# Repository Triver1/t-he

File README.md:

# Tot-HE-m

Tot-HE-m is a hall-effect version of [GEIGEIGEIST's TOTEM](https://github.com/GEIGEIGEIST/TOTEM): the same
38-key split layout, scaled to MX spacing, with a linear hall sensor under every switch instead of a mechanical
contact. The goal is an analog keyboard that is cheap and easy to build at home. Each half is one two-layer PCB
with a handful of SMD parts, a Seeed XIAO RP2040 and a 3D printed case, so everything can be ordered from LCSC,
JLCPCB and the usual keyboard shops, and soldered with an ordinary iron.

## Features

- **Hall-effect sensing on every key**, read through three 74HC4051 multiplexers per half. Tested with MMD C1
  switches; other MX-style magnetic switches (Gateron KS-20, Wooting Lekker and similar) should work as well.
- **Auto calibration.** Each key measures its rest position at power-up and learns where it bottoms out while you
  type; the learnt travel is kept across reboots.
- **Adjustable actuation and release points**, set as key depth in tenths of a millimetre.
- **Rapid trigger**, with separate press and release sensitivity.
- **VIA support**: remap keys and change all of the above live from the browser.
- **Controller layer**: turns W A S D into an analog gamepad stick, so a light press walks and a full press runs.

## Cost

Rough prices for one keyboard, checked October 2026, in euros, before shipping and taxes. Several parts only come
in larger quantities, so ordering for two or more keyboards brings the price per board down a lot.

| Part | Where | Approx. |
| --- | --- | ---: |
| PCBs (5 sets) | JLCPCB | 30 |
| Sensors, muxes, capacitors, TRRS jacks | LCSC | 15 |
| 2x Seeed XIAO RP2040 | Seeed or any electronics shop | 15 |
| 38 magnetic switches | keyboard shop | 20 |
| 38 MX keycaps | keyboard shop | 20 |
| TRRS cable, USB-C cable | any | 10 |
| 8x M2 x 10 screws, rubber bumpers | hardware shop | 5 |
| About 150 g of filament | | 3 |
| **Total** | | **≈ 120** |

## Ordering

**PCB (JLCPCB).** Upload [`production/Tot-HE-m_gerbers.zip`](production/Tot-HE-m_gerbers.zip) on jlcpcb.com. The
file holds both halves side by side, so an order of 5 gives 5 left and 5 right boards. Settings: 2 layers, 1.6 mm,
1 oz copper, any colour; the defaults cover the rest. JLCPCB counts the two outlines as two designs and adds a small
fee for the second, which shows up in the quote. Pick "Remove order number", or it gets printed on the silkscreen.

**Parts (LCSC).** On lcsc.com, open the BOM tool, upload [`production/lcsc_bom.csv`](production/lcsc_bom.csv) and
match the "LCSC Part Number" column. That puts every SMD part and both jacks in the cart in one go, with a few
spares for the small parts:

| Part | LCSC | Per half |
| --- | --- | ---: |
| TI DRV5055A3QDBZR linear hall sensor, SOT-23 | C266128 | 19 |
| 74HC4051D analog mux, SOIC-16 | C9386 | 3 |
| 100 nF capacitor, 0805 | C1711 | 22 |
| PJ-320A TRRS jack | C2884926 | 1 |

**Everything else:** two Seeed XIAO RP2040s, 38 magnetic switches, 38 MX keycaps, a 4-pole TRRS cable, a USB-C
cable, eight M2 x 10 screws and at least eight rubber bumpers taller than 2.5 mm.

The cable has to be **TRRS** (three insulating rings on the plug). A 3-pole TRS cable bridges two contacts in the
jack and shorts the 3.3 V supply, and the keyboard stays dark.

## Building

1. Solder the bottom side first: one hall sensor under every switch position, the three muxes and the capacitors.
   The sensors are wired pin 1 VCC, 2 OUT, 3 GND, the DRV5055's own SOT-23 order.
2. Solder the XIAO flat on its castellated pads, without headers, and the TRRS jack on top. Check every XIAO pad,
   GND and D8 to D10 in particular: a dry joint there makes all keys read wrong.
3. Flash the firmware (below) and check that every key types before closing the case.
4. Clip the switches into the printed plate, put the plate on the PCB, drop the shell over it and fasten each
   corner with an M2 x 10 screw from below, then stick the bumpers on.

Only plug or unplug the TRRS cable with USB disconnected.

## Firmware and VIA

The firmware is QMK. Hold the XIAO's BOOT button while plugging a half in; it shows up as a drive called RPI-RP2.
Copy [`firmware/uf2/tot_he_m_via_left.uf2`](firmware/uf2) onto the left half and `tot_he_m_via_right.uf2` onto the
right. Each image stores its side on first boot. Afterwards, hold Esc and press T to get back into the bootloader.

To configure it in VIA:

1. Open [usevia.app](https://usevia.app) in a Chromium-based browser.
2. Under Settings, turn on **Show Design tab**.
3. In the **Design** tab, load [`firmware/via/tot-he-m.json`](firmware/via/tot-he-m.json). VIA forgets it when the
   browser closes, so load it again next time.
4. In **Configure**, click Authorize device and pick Tot-HE-m.

The keymap editor then works as on any VIA keyboard, and the **Hall effect** menu has the analog settings:

| Setting | Range | Default |
| --- | --- | --- |
| Actuation point | 1.0 to 3.8 mm | 2.0 mm |
| Release point | 0.8 mm up to 0.2 mm shallower than actuation | 1.6 mm |
| Rapid trigger | on / off | off |
| Rapid trigger press and release sensitivity | 0.2 to 2.0 mm | 0.3 mm |
| Stick dead zone (controller layer) | 0 to 2.0 mm | 0 |
| Stick full deflection (controller layer) | 0.5 to 4.0 mm | 3.8 mm |

Settings are stored on the half that is plugged in, which sends them to the other half. On Linux, the browser needs
access to the keyboard's hidraw device; a udev rule for vendor `746d`, product `7e57` with `TAG+="uaccess"` does it.

The default keymap follows a Ferris Sweep layout: QWERTY with Ctrl and Alt on the outer bottom keys and, on the
thumbs, Shift, Space and Esc on the left, Enter, Backspace and GUI on the right. Holding Backspace gives numbers and
symbols, Enter navigation and F-keys, Esc system keys. Hold Esc and press G for the controller layer.

To build the firmware yourself, copy `firmware/qmk/tot_he_m` into `keyboards/` of a QMK checkout and run, for each
half:

```bash
qmk compile -kb tot_he_m -km via -e EXTRAFLAGS=-DINIT_EE_HANDS_LEFT -e TARGET=tot_he_m_via_left
qmk compile -kb tot_he_m -km via -e EXTRAFLAGS=-DINIT_EE_HANDS_RIGHT -e TARGET=tot_he_m_via_right
```

## Case

Each half is a shell and a switch plate, both printed without supports: the shell deck-down, the plate top-down.
The stack is the 1.6 mm PCB, the plate 5 mm above it and the deck 6 mm above the plate, 12.6 mm in total. Each
M2 x 10 screw goes up from under the PCB, through the plate's standoff, and cuts its own thread in a pilot hole in
the deck. The screw heads sit under the PCB, so the bumpers need to be taller than 2.5 mm. For a case that gets
opened often, set `insert = true` in `case/totem_he_case.scad` to use M2 heat-set inserts instead.

The foam mold casts an optional silicone foam layer between the PCB and the plate, which dampens the sound; the
instructions are at the top of `case/foam_mold.scad`.

The carry case holds both halves face to face in one frame, with a lid on each side that hangs on two lift-off hook
hinges and clicks shut on the thumb side; `case/carry_case.scad` explains the parts. Measure `keycap_h` and `bumper_h`
at the top of that file before printing. The frame comes with faceted scales (`totemhe_carry_frame.stl`) or 45 degree
stripes (`totemhe_carry_frame_stripes.stl`) on its outer face. The texture is generated by `case/wall_texture.py`:
export `lid2d()` from `carry_case.scad` as an SVG, run `python3 case/wall_texture.py outline.svg case/wall_texture.scad
scales` (or `stripes`), then export the frame.

The STLs are in `case/stl`, made from the OpenSCAD sources (OpenSCAD 2025 or newer):

```bash
openscad --enable=roof -D 'part="shell"' -D 'side="left"' -o case/stl/totemhe_shell_left.stl case/totem_he_case.scad
```

## Repository

| Folder | Contents |
| --- | --- |
| `pcb/` | KiCad project with both halves, and the Ergogen config and footprints the board layout was generated from |
| `production/` | Gerbers for JLCPCB and the LCSC BOM |
| `case/` | OpenSCAD sources and STLs for the shell, plate, foam mold and carry case |
| `firmware/` | QMK source, prebuilt images and the VIA definition |

## License

The PCB, case and everything else outside `firmware/` are licensed under
[CC BY-NC-SA 4.0](LICENSE), like TOTEM, which they are derived from: share and adapt them freely for
non-commercial use, with attribution, under the same license. The firmware in `firmware/` is
[GPL-2.0-or-later](firmware/LICENSE), like QMK.

## Credits

Layout and outline from [TOTEM](https://github.com/GEIGEIGEIST/TOTEM) by GEIGEIGEIST. The sensor scan is modelled
on Boardloaf-HE, the per-key calibration on Hector. Some footprints are adapted from ceoloide's Ergogen footprints
(see `pcb/footprints/LICENSE-ceoloide`).

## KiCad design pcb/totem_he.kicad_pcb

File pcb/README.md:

# Tot-HE-m PCB

Hall-effect version of TOTEM's layout at MX spacing. `totem_he.kicad_pcb` holds both halves side by side, so one
order covers both; open `totem_he.kicad_pro` beside it so KiCad loads the design rules. Both halves are placed and
routed (see Mux placement and routing).

The board is generated with Ergogen: `./build.sh` rebuilds it from the case geometry, `mux_map.json` and the
footprint modules in `footprints/`, then checks it. See "Generating the board" below.

## Layout

| Face | Parts |
| --- | --- |
| Front (top) | Switches, XIAO RP2040 (soldered flat on its castellations over plated holes), PJ-320A TRRS jack |
| Back (underside) | 19 sensors, 19 sensor capacitors, 3 muxes and their capacitors |

- The sensors sit under the board, on the face opposite the switches, like HE60. The SOT-23 pads are
  Boardloaf-HE's 1.69 x 0.6 mm, which are easy to hand-solder.
- The right half is the left mirrored about x = `AXIS_X` in `halves.py`, 5 mm from the left's inner edge. Each
  part is turned to minus its angle but not mirrored, so every land pattern stays correct and both halves put the
  same parts on the same faces. USB-C faces the outer edge on each half.
- References: S1 to S19, IC1 to IC3, MCU1, TRRS1 and H1 to H4 on the left; the right adds 100 (S101, IC101, ...).
  Nets carry their half's prefix (`L/VCC`, `R/VCC`), so the halves share no net and DRC treats them separately.
- The PJ-320A footprint has pads 2 (sleeve, GND), 3 (ring 2, DATA) and 4 (tip, VCC) in two mirrored columns, pad 4
  slotted to take the ring 1 leg as well, so the jack fits either way round.

Together the halves are 265 x 103 mm; each is 128.9 x 103.0 mm.

## Mux placement and routing

Each half has one mux per finger group, on the underside between the columns it serves: IC1 takes the outer,
pinky and ring keys (ADC_A, D0), IC2 middle and index (ADC_B, D2), IC3 inner and thumbs (ADC_C, D1). Its position
and angle are the `at` entry in `mux_map.json`, chosen with at least 1 mm clear of every pad and peg hole. The
channels follow the order the sensors sit around the mux, so the sensor lines fan in without crossing; where that
needs a hand-set order, `mux_map.json` marks the mux `fixed`. The firmware has a channel map for each half.

The routing is hand-designed and written out in `routes.py`: every trace as waypoints, 45 degree bends, sensor
patterns in each switch's own frame. `build.sh` applies it, so a regenerated board comes out routed.

| Layer | Nets |
| --- | --- |
| Underside | Signals: each sensor's output fanning into its mux, the bus from the XIAO along the top edge (data, select lines, two mux outputs) up through the notch above the middle-top key, short power stubs at each part |
| Top | 3.3 V and ground as two interleaved combs: a 3.3 V rail along the top edge with a tooth down each column, ground teeth up each column joined by a rail along the bottom edge; no fills |

Every switch has two tented vias in its footprint (3.3 V right of the sensor, ground left), so each sensor reaches
both combs. Where a bus line branches to IC1 or IC2, it takes a via up and runs on the top layer between the power
teeth; on the right half, IC2's output and the data line each hop one stretch on top the same way. 0.25 mm
signals, 0.4 mm power stubs, 0.5 mm rails.

`route.py` (run as `./r`) is the tool the routing was drawn with: `./r view [x0 y0 x1 y1]` draws a region with
open connections dashed, `./r open` lists them, `./r track`, `./r via`, `./r delete` and `./r undo` edit, and
`./r drc` summarises. To change the routing, edit `routes.py` and run `./build.sh`.

## Electronics

Same scheme as Boardloaf-HE.

| Part | Per half | Notes |
| --- | --- | --- |
| Linear hall sensor, SOT-23: TI DRV5055A3QDBZR (LCSC C266128) | 19 | Under each stem magnet. Pin 1 VCC, 2 OUT, 3 GND |
| 100 nF 0805 (C1711) | 22 | One per sensor and per mux |
| 74HC4051 SOIC-16 (C9386) | 3 | One per ADC input |
| XIAO RP2040 | 1 | Soldered flat, no headers. Its pads have 1.0 mm plated holes, so every pin reaches the underside without a via and solder wicks in. USB-C over the outer edge |
| PJ-320A TRRS | 1 | Tip VCC, ring 1 tied to tip, ring 2 DATA, sleeve GND |
| M2 plated holes | 4 | Case screws |

XIAO pins: D0, D1, D2 read the three muxes (IC1, IC3, IC2). D8, D9, D10 drive the shared select lines S0 to S2.
D7 is the split link, one half-duplex wire on TRRS ring 2; D3 to D6 and 5V are unconnected. 3V3 powers the sensors and
muxes and feeds the other half over the tip. Which key sits on which mux channel is in `mux_map.json`, per half.

DRV5055A3 (TI datasheet SBAS640C): 3.0 to 3.63 V, rests at 1.65 V, 15 mV/mT at 3.3 V, 2 mA typical and 4 mA
maximum, at least 10 nF on VCC (the 100 nF beside each sensor covers it). Under the board the sensor is 1.6 mm
further from the magnet than on top; the firmware learns each key's travel, so a smaller swing costs resolution,
not function. Before ordering a full set, check one part: 3.3 V on pin 1, ground on pin 3, and pin 2 near 1.65 V,
swinging when a magnet approaches.

## Checks

Run these in the KiCad 8 container, and again after routing:

- `netcheck.py` checks every pad's net against the design on each half, and that no net crosses between them: sensor pin order, each sensor output on
  its mux channel from `mux_map.json`, mux commons, select lines, enable and supply pins, the XIAO and the TRRS.
- `../firmware/gen_firmware.py` follows every connection the firmware relies on in each half, requires both halves
  on the same XIAO pins, and compares them with `mux_map.json`.
- `./r drc` runs KiCad's design rule check on the routed board.

## Ordering

Two scripts write JLCPCB order files; both run KiCad 8 in Docker and need a clean DRC.

```bash
./gerbers.sh       # both halves joined by snap-off tabs (panel.py), zipped as Tot-HE-m_jlcpcb_gerbers.zip
./production.sh    # the two halves as they sit in the file, zipped as production/THE_gerbers.zip
```

With `gerbers.sh` both halves arrive as one panel, broken apart along the tabs (JLCPCB may still count two
different boards on a panel as two designs; the quote shows it). With `production.sh` an order of 5 gives 5 left and 5 right boards. JLCPCB counts the two outlines as two
designs and adds a fee for the second (their help page, "What Counts as Different Designs", gives no amount; the
quote shows it), so compare the quote with two separate orders. Settings: 2 layers, 1.6 mm FR-4, 1 oz copper; the defaults cover the rest (0.25 mm
tracks, 0.2 mm clearance, 0.3 mm vias). Choose "Remove order number", or JLCPCB prints one on the silkscreen. The
Gerbers follow JLCPCB's KiCad guide: Protel extensions, solder mask subtracted from silkscreen, one Excellon file
for plated and unplated holes, the alternate drill mode for the slotted TRRS pad.

## Generating the board

```bash
./build.sh
```

replaces `totem_he.kicad_pcb` with a freshly generated, routed board (`./build.sh other.kicad_pcb` writes elsewhere).
It runs Ergogen, KiCad and OpenSCAD in Docker:

1. `gen_config.py` writes `config.yaml` for Ergogen. Key, XIAO, jack and hole positions come from
   `../case/totem_geometry.scad`; the right half is the left mirrored about `halves.AXIS_X`, each part turned to minus
   its angle but not mirrored. Each mux's position is the `at` entry in `mux_map.json` (board x, y, angle, per
   half); the script works out its channels and writes them back to `mux_map.json`. Every net gets its half's
   prefix (`L/`, `R/`).
2. Ergogen builds both halves into one board from `config.yaml` and the modules in `footprints/` (switch with its
   sensor and capacitor, mux, XIAO, TRRS jack, mounting hole).
3. `finish.py` renumbers the right half (S101, IC101, ...) and saves the board in KiCad 8's format.
4. `set_edge.py` adds both outlines from the case's PCB shape (`openscad -D 'part="pcb"'`).
5. `mkpro.py` writes the design rules, `netcheck.py` checks the nets, `gen_mock.py` writes the PCB mock's part list.

Generating discards any routing, so change the layout before routing; after that, edit the board in KiCad.
`set_edge.py pcb2d.svg <in> <out>` also works on a routed board, for outline changes, and prints how far the edge
moved. Write the `.kicad_pro` (`mkpro.py`) before filling any pours, or KiCad fills to its default 0.5 mm edge
clearance instead of 0.25 mm.

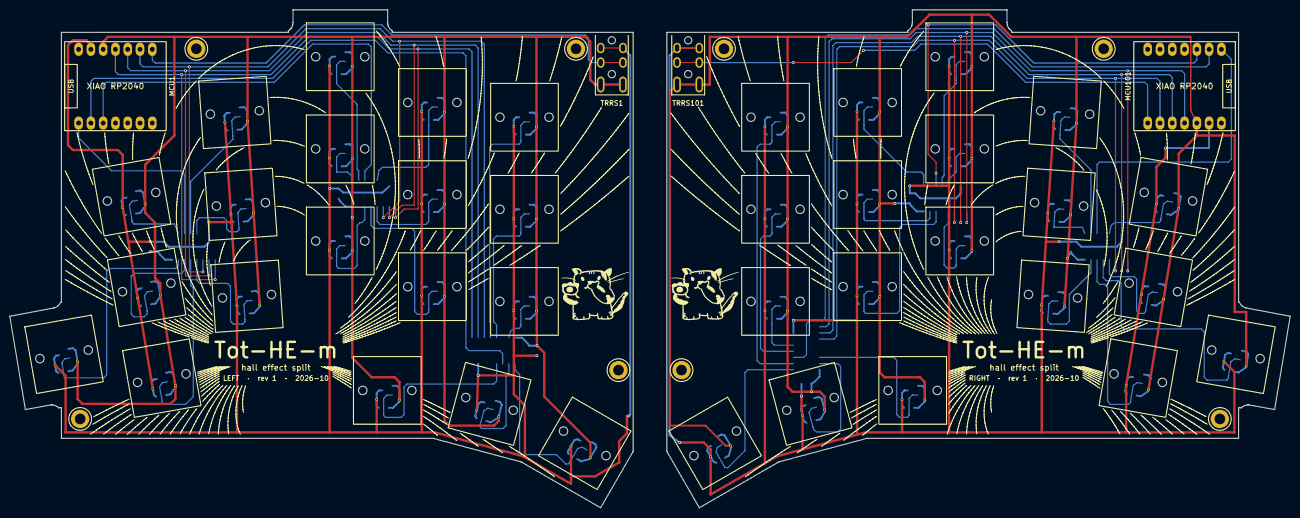
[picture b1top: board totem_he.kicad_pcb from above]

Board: 2 copper layers, 264.8 x 103.0 mm, 56 parts (0 on the bottom side), 56 nets.

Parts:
H1, H2, H3, H4, H101, H102, H103, H104: mounting_hole_plated
IC1, IC2, IC3, IC101, IC102, IC103: mux_4051
MCU1, MCU101: xiao_rp2040
S1, S2, S3, S4, S5, S6, S7, S8, S9, S10, S11, S12, S13, S14, S15, S16, S17, S18, S19, S101, S102, S103, S104, S105, S106, S107, S108, S109, S110, S111, S112, S113, S114, S115, S116, S117, S118, S119: switch_he
TRRS1, TRRS101: trrs_pj320a

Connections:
L/ADC_A: IC1.3, MCU1.1
L/ADC_B: IC2.3, MCU1.3
L/ADC_C: IC3.3, MCU1.2
L/DATA: MCU1.8, TRRS1.3
L/GND: IC1.6, IC1.7, IC1.8, IC1.C2, IC2.6, IC2.7, IC2.8, IC2.C2, IC3.6, IC3.7, IC3.8, IC3.C2, MCU1.13, S1.3, S1.C2, S2.3, S2.C2, S3.3, S3.C2, S4.3, S4.C2, S5.3, S5.C2, S6.3, S6.C2, S7.3, S7.C2, S8.3, S8.C2, S9.3, S9.C2, S10.3, S10.C2, S11.3, S11.C2, S12.3, S12.C2, S13.3, S13.C2, S14.3, S14.C2, S15.3, S15.C2, S16.3, S16.C2, S17.3, S17.C2, S18.3, S18.C2, S19.3, S19.C2, TRRS1.2
L/K_INDEX_BOTTOM: IC2.13, S14.2
L/K_INDEX_HOME: IC2.12, S9.2
L/K_INDEX_TOP: IC2.5, S4.2
L/K_INNER_BOTTOM: IC3.15, S15.2
L/K_INNER_HOME: IC3.13, S10.2
L/K_INNER_TOP: IC3.12, S5.2
L/K_MIDDLE_BOTTOM: IC2.14, S13.2
L/K_MIDDLE_HOME: IC2.1, S8.2
L/K_MIDDLE_TOP: IC2.2, S3.2
L/K_OUTER: IC1.15, S16.2
L/K_PINKY_BOTTOM: IC1.13, S11.2
L/K_PINKY_HOME: IC1.14, S6.2
L/K_PINKY_TOP: IC1.2, S1.2
L/K_RING_BOTTOM: IC1.12, S12.2
L/K_RING_HOME: IC1.5, S7.2
L/K_RING_TOP: IC1.4, S2.2
L/K_THUMB1: IC3.4, S17.2
L/K_THUMB2: IC3.2, S18.2
L/K_THUMB3: IC3.1, S19.2
L/SEL0: IC1.11, IC2.11, IC3.11, MCU1.9
L/SEL1: IC1.10, IC2.10, IC3.10, MCU1.10
L/SEL2: IC1.9, IC2.9, IC3.9, MCU1.11
L/VCC: IC1.16, IC1.C1, IC2.16, IC2.C1, IC3.16, IC3.C1, MCU1.12, S1.1, S1.C1, S2.1, S2.C1, S3.1, S3.C1, S4.1, S4.C1, S5.1, S5.C1, S6.1, S6.C1, S7.1, S7.C1, S8.1, S8.C1, S9.1, S9.C1, S10.1, S10.C1, S11.1, S11.C1, S12.1, S12.C1, S13.1, S13.C1, S14.1, S14.C1, S15.1, S15.C1, S16.1, S16.C1, S17.1, S17.C1, S18.1, S18.C1, S19.1, S19.C1, TRRS1.4
R/ADC_A: IC101.3, MCU101.1
R/ADC_B: IC102.3, MCU101.3
R/ADC_C: IC103.3, MCU101.2
R/DATA: MCU101.8, TRRS101.3
R/GND: IC101.6, IC101.7, IC101.8, IC101.C2, IC102.6, IC102.7, IC102.8, IC102.C2, IC103.6, IC103.7, IC103.8, IC103.C2, MCU101.13, S101.3, S101.C2, S102.3, S102.C2, S103.3, S103.C2, S104.3, S104.C2, S105.3, S105.C2, S106.3, S106.C2, S107.3, S107.C2, S108.3, S108.C2, S109.3, S109.C2, S110.3, S110.C2, S111.3, S111.C2, S112.3, S112.C2, S113.3, S113.C2, S114.3, S114.C2, S115.3, S115.C2, S116.3, S116.C2, S117.3, S117.C2, S118.3, S118.C2, S119.3, S119.C2, TRRS101.2
R/K_INDEX_BOTTOM: IC102.14, S114.2
R/K_INDEX_HOME: IC102.15, S109.2
R/K_INDEX_TOP: IC102.1, S104.2
R/K_INNER_BOTTOM: IC103.5, S115.2
R/K_INNER_HOME: IC103.4, S110.2
R/K_INNER_TOP: IC103.2, S105.2
R/K_MIDDLE_BOTTOM: IC102.12, S113.2
R/K_MIDDLE_HOME: IC102.5, S108.2
R/K_MIDDLE_TOP: IC102.4, S103.2
R/K_OUTER: IC101.13, S116.2
R/K_PINKY_BOTTOM: IC101.14, S111.2
R/K_PINKY_HOME: IC101.12, S106.2
R/K_PINKY_TOP: IC101.5, S101.2
R/K_RING_BOTTOM: IC101.15, S112.2
R/K_RING_HOME: IC101.1, S107.2
R/K_RING_TOP: IC101.2, S102.2
R/K_THUMB1: IC103.14, S117.2
R/K_THUMB2: IC103.15, S118.2
R/K_THUMB3: IC103.1, S119.2
R/SEL0: IC101.11, IC102.11, IC103.11, MCU101.9
R/SEL1: IC101.10, IC102.10, IC103.10, MCU101.10
R/SEL2: IC101.9, IC102.9, IC103.9, MCU101.11
R/VCC: IC101.16, IC101.C1, IC102.16, IC102.C1, IC103.16, IC103.C1, MCU101.12, S101.1, S101.C1, S102.1, S102.C1, S103.1, S103.C1, S104.1, S104.C1, S105.1, S105.C1, S106.1, S106.C1, S107.1, S107.C1, S108.1, S108.C1, S109.1, S109.C1, S110.1, S110.C1, S111.1, S111.C1, S112.1, S112.C1, S113.1, S113.C1, S114.1, S114.C1, S115.1, S115.C1, S116.1, S116.C1, S117.1, S117.C1, S118.1, S118.C1, S119.1, S119.C1, TRRS101.4

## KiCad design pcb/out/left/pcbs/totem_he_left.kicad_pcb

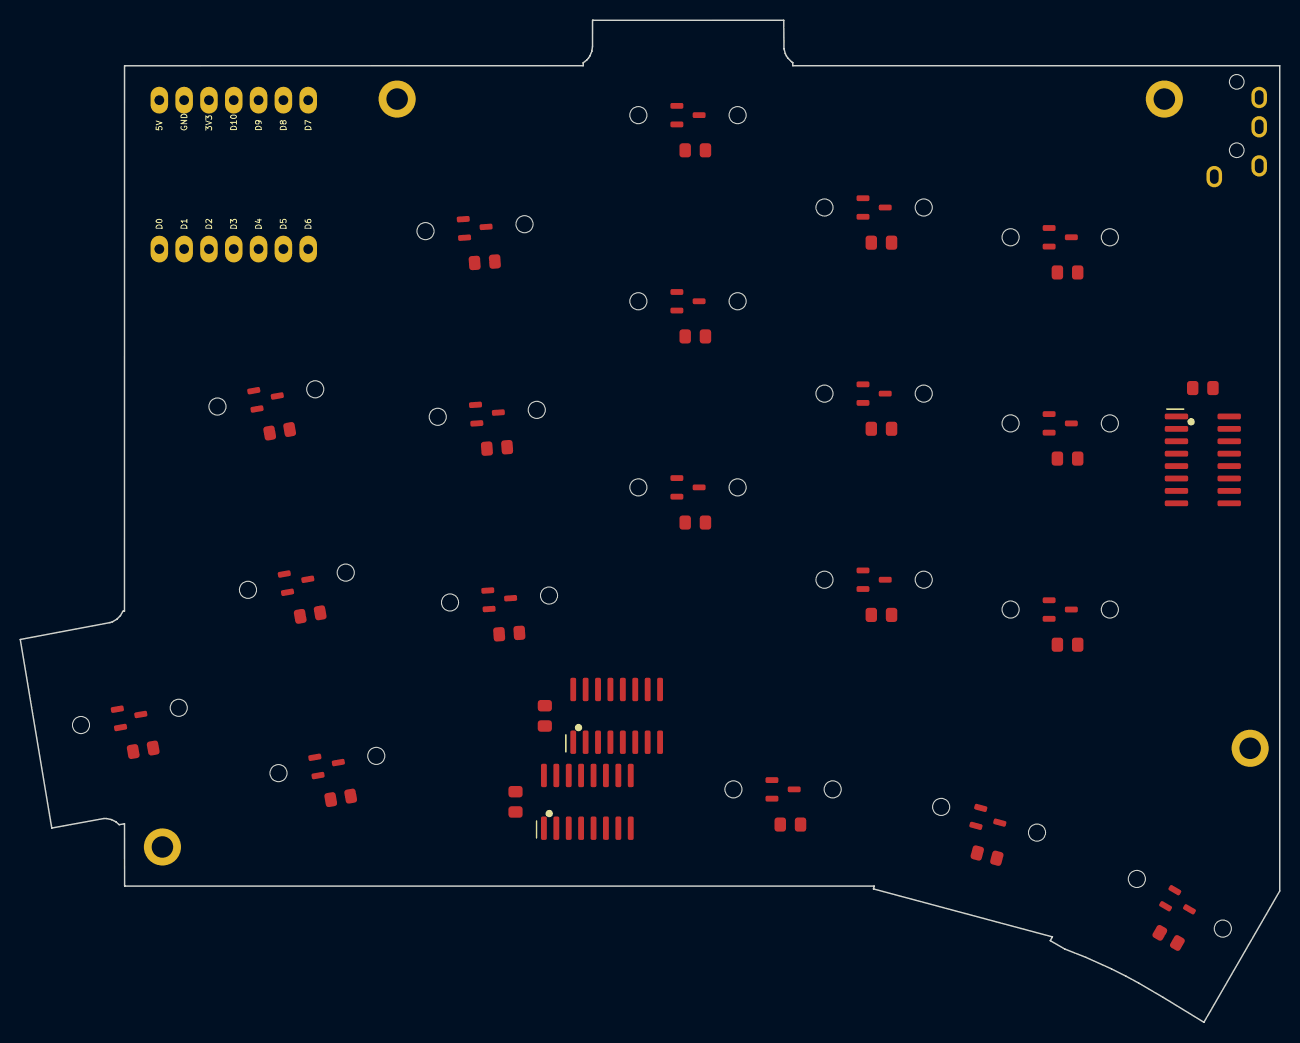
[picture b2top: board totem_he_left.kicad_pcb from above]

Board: 2 copper layers, 128.9 x 102.6 mm, 28 parts (0 on the bottom side), 30 nets, no tracks yet.

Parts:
H1, H2, H3, H4: mounting_hole_plated
IC1, IC2, IC3: mux_4051
MCU1: xiao_rp2040
S1, S2, S3, S4, S5, S6, S7, S8, S9, S10, S11, S12, S13, S14, S15, S16, S17, S18, S19: switch_he
TRRS1: trrs_pj320a

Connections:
ADC_A: IC1.3, MCU1.1
ADC_B: IC2.3, MCU1.2
ADC_C: IC3.3, MCU1.3
GND: IC1.6, IC1.7, IC1.8, IC1.C2, IC2.6, IC2.7, IC2.8, IC2.C2, IC3.6, IC3.7, IC3.8, IC3.C2, MCU1.13, S1.2, S1.C2, S2.2, S2.C2, S3.2, S3.C2, S4.2, S4.C2, S5.2, S5.C2, S6.2, S6.C2, S7.2, S7.C2, S8.2, S8.C2, S9.2, S9.C2, S10.2, S10.C2, S11.2, S11.C2, S12.2, S12.C2, S13.2, S13.C2, S14.2, S14.C2, S15.2, S15.C2, S16.2, S16.C2, S17.2, S17.C2, S18.2, S18.C2, S19.2, S19.C2, TRRS1.2
K_INDEX_BOTTOM: IC2.12, S10.3
K_INDEX_HOME: IC2.1, S11.3
K_INDEX_TOP: IC2.5, S12.3
K_INNER_BOTTOM: IC3.13, S13.3
K_INNER_HOME: IC3.14, S14.3
K_INNER_TOP: IC3.15, S15.3
K_MIDDLE_BOTTOM: IC2.13, S7.3
K_MIDDLE_HOME: IC2.14, S8.3
K_MIDDLE_TOP: IC2.15, S9.3
K_OUTER: IC1.12, S16.3
K_PINKY_BOTTOM: IC1.13, S1.3
K_PINKY_HOME: IC1.14, S2.3
K_PINKY_TOP: IC1.15, S3.3
K_RING_BOTTOM: IC1.1, S4.3
K_RING_HOME: IC1.5, S5.3
K_RING_TOP: IC1.2, S6.3
K_THUMB1: IC2.2, S17.3
K_THUMB2: IC2.4, S18.3
K_THUMB3: IC3.12, S19.3
RX: MCU1.8, TRRS1.3
SEL0: IC1.11, IC2.11, IC3.11, MCU1.5
SEL1: IC1.10, IC2.10, IC3.10, MCU1.6
SEL2: IC1.9, IC2.9, IC3.9, MCU1.9
TX: MCU1.7, TRRS1.5
VCC: IC1.16, IC1.C1, IC2.16, IC2.C1, IC3.16, IC3.C1, MCU1.12, S1.1, S1.C1, S2.1, S2.C1, S3.1, S3.C1, S4.1, S4.C1, S5.1, S5.C1, S6.1, S6.C1, S7.1, S7.C1, S8.1, S8.C1, S9.1, S9.C1, S10.1, S10.C1, S11.1, S11.C1, S12.1, S12.C1, S13.1, S13.C1, S14.1, S14.C1, S15.1, S15.C1, S16.1, S16.C1, S17.1, S17.C1, S18.1, S18.C1, S19.1, S19.C1, TRRS1.4
Y7: IC1.4, IC3.4

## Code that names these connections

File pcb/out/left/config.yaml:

meta:
  engine: 4.1.0
  name: totem_he_left
units:
  u: 19.05
points:
  zones:
    origin:
      anchor: {shift: [0, 0]}
      columns: {o: }
      rows: {r: {tags: [helper]}}
    pinky:
      anchor: {shift: [31.394, -76.180], rotate: 10.000}
      key: {padding: u, tags: [alpha]}
      columns: {c: }
      rows:
        bottom: {name: pinky_bottom, out_net: K_PINKY_BOTTOM}
        home: {name: pinky_home, out_net: K_PINKY_HOME, adjust: {shift: [0.181, -0.032]}}
        top: {name: pinky_top, out_net: K_PINKY_TOP, adjust: {shift: [0.362, -0.063]}}
    ring:
      anchor: {shift: [49.013, -59.240], rotate: 4.000}
      key: {padding: u, tags: [alpha]}
      columns: {c: }
      rows:
        bottom: {name: ring_bottom, out_net: K_RING_BOTTOM}
        home: {name: ring_home, out_net: K_RING_HOME, adjust: {shift: [0.074, -0.005]}}
        top: {name: ring_top, out_net: K_RING_TOP, adjust: {shift: [0.147, -0.009]}}
    middle:
      anchor: {shift: [68.303, -47.815], rotate: 0.000}
      key: {padding: u, tags: [alpha]}
      columns: {c: }
      rows:
        bottom: {name: middle_bottom, out_net: K_MIDDLE_BOTTOM}
        home: {name: middle_home, out_net: K_MIDDLE_HOME, adjust: {shift: [0.000, 0.001]}}
        top: {name: middle_top, out_net: K_MIDDLE_TOP, adjust: {shift: [0.000, 0.001]}}
    index:
      anchor: {shift: [87.353, -57.268], rotate: 0.000}
      key: {padding: u, tags: [alpha]}
      columns: {c: }
      rows:
        bottom: {name: index_bottom, out_net: K_INDEX_BOTTOM}
        home: {name: index_home, out_net: K_INDEX_HOME}
        top: {name: index_top, out_net: K_INDEX_TOP}
    inner:
      anchor: {shift: [106.403, -60.316], rotate: 0.000}
      key: {padding: u, tags: [alpha]}
      columns: {c: }
      rows:
        bottom: {name: inner_bottom, out_net: K_INNER_BOTTOM}
        home: {name: inner_home, out_net: K_INNER_HOME}
        top: {name: inner_top, out_net: K_INNER_TOP}
    outer:
      anchor: {shift: [11.178, -71.258], rotate: 10.000}
      key: {padding: u, tags: [alpha]}
      columns: {c: }
      rows:
        k: {name: outer, out_net: K_OUTER}
    thumb1:
      anchor: {shift: [78.034, -78.725], rotate: 0.000}
      key: {padding: u, tags: [thumb]}
      columns: {c: }
      rows:
        k: {name: thumb1, out_net: K_THUMB1}
    thumb2:
      anchor: {shift: [99.120, -81.835], rotate: -15.000}
      key: {padding: u, tags: [thumb]}
      columns: {c: }
      rows:
        k: {name: thumb2, out_net: K_THUMB2}
    thumb3:
      anchor: {shift: [118.647, -90.435], rotate: -30.000}
      key: {padding: u, tags: [thumb]}
      columns: {c: }
      rows:
        k: {name: thumb3, out_net: K_THUMB3}
outlines:
  board:
    - what: polygon
      operation: add
      points:
        - {ref: origin_o_r, shift: [78.892, -4.243]}
        - {ref: origin_o_r, shift: [78.523, -3.874]}
        - {ref: origin_o_r, shift: [78.378, -3.656]}
        - {ref: origin_o_r, shift: [78.262, -3.421]}
        - {ref: origin_o_r, shift: [78.127, -2.917]}
        - {ref: origin_o_r, shift: [78.105, -0.004]}
        - {ref: origin_o_r, shift: [58.599, -0.007]}
        - {ref: origin_o_r, shift: [58.537, -0.011]}
        - {ref: origin_o_r, shift: [58.533, -0.072]}
        - {ref: origin_o_r, shift: [58.532, -2.657]}
        - {ref: origin_o_r, shift: [58.464, -3.174]}
        - {ref: origin_o_r, shift: [58.264, -3.656]}
        - {ref: origin_o_r, shift: [58.119, -3.874]}
        - {ref: origin_o_r, shift: [57.946, -4.071]}
        - {ref: origin_o_r, shift: [57.578, -4.358]}
        - {ref: origin_o_r, shift: [57.578, -4.656]}
        - {ref: origin_o_r, shift: [10.631, -4.661]}
        - {ref: origin_o_r, shift: [10.625, -60.465]}
        - {ref: origin_o_r, shift: [10.472, -60.492]}
        - {ref: origin_o_r, shift: [10.212, -60.942]}
        - {ref: origin_o_r, shift: [9.843, -61.311]}
        - {ref: origin_o_r, shift: [9.390, -61.572]}
        - {ref: origin_o_r, shift: [9.143, -61.656]}
        - {ref: origin_o_r, shift: [-0.041, -63.383]}
        - {ref: origin_o_r, shift: [3.182, -82.683]}
        - {ref: origin_o_r, shift: [8.522, -81.707]}
        - {ref: origin_o_r, shift: [8.783, -81.710]}
        - {ref: origin_o_r, shift: [9.294, -81.818]}
        - {ref: origin_o_r, shift: [9.760, -82.055]}
        - {ref: origin_o_r, shift: [10.087, -82.341]}
        - {ref: origin_o_r, shift: [10.628, -82.245]}
        - {ref: origin_o_r, shift: [10.638, -88.626]}
        - {ref: origin_o_r, shift: [87.362, -88.625]}
        - {ref: origin_o_r, shift: [87.285, -88.913]}
        - {ref: origin_o_r, shift: [105.606, -93.822]}
        - {ref: origin_o_r, shift: [105.383, -94.209]}
        - {ref: origin_o_r, shift: [106.860, -95.061]}
        - {ref: origin_o_r, shift: [109.039, -95.922]}
        - {ref: origin_o_r, shift: [111.649, -97.099]}
        - {ref: origin_o_r, shift: [113.151, -97.855]}
        - {ref: origin_o_r, shift: [114.431, -98.548]}
        - {ref: origin_o_r, shift: [116.943, -100.017]}
        - {ref: origin_o_r, shift: [121.112, -102.565]}
        - {ref: origin_o_r, shift: [128.870, -89.128]}
        - {ref: origin_o_r, shift: [128.870, -4.657]}
        - {ref: origin_o_r, shift: [79.028, -4.656]}
        - {ref: origin_o_r, shift: [79.028, -4.333]}
  plate:
    - what: outline
      name: board
    - what: rectangle
      operation: subtract
      where: [alpha, thumb]
      size: 14
pcbs:
  totem_he_left:
    template: kicad8
    outlines:
      main: {outline: board}
    footprints:
      - what: switch_he
        where: [alpha, thumb]
        params: {VCC: VCC, GND: GND, OUT: "{{out_net}}"}
      - what: mux_4051
        where: {ref: origin_o_r, shift: [58.000, -80.000], rotate: 90.000}
        params: {VCC: VCC, GND: GND, Z: ADC_A, S0: SEL0, S1: SEL1, S2: SEL2, Y0: K_PINKY_BOTTOM, Y1: K_PINKY_HOME, Y2: K_PINKY_TOP, Y3: K_OUTER, Y4: K_RING_BOTTOM, Y5: K_RING_HOME, Y6: K_RING_TOP}
      - what: mux_4051
        where: {ref: origin_o_r, shift: [61.000, -71.200], rotate: 90.000}
        params: {VCC: VCC, GND: GND, Z: ADC_B, S0: SEL0, S1: SEL1, S2: SEL2, Y0: K_MIDDLE_BOTTOM, Y1: K_MIDDLE_HOME, Y2: K_MIDDLE_TOP, Y3: K_INDEX_BOTTOM, Y4: K_INDEX_HOME, Y5: K_INDEX_TOP, Y6: K_THUMB1, Y7: K_THUMB2}
      - what: mux_4051
        where: {ref: origin_o_r, shift: [121.000, -45.000], rotate: 0.000}
        params: {VCC: VCC, GND: GND, Z: ADC_C, S0: SEL0, S1: SEL1, S2: SEL2, Y0: K_INNER_BOTTOM, Y1: K_INNER_HOME, Y2: K_INNER_TOP, Y3: K_THUMB3}
      - what: xiao_rp2040
        where: {ref: origin_o_r, shift: [21.811, -15.801], rotate: 90.000}
        params: {D0: ADC_A, D1: ADC_B, D2: ADC_C, D4: SEL0, D5: SEL1, D8: SEL2, D6: TX, D7: RX, V3: VCC, GND: GND}
      - what: ceoloide/trrs_pj320a
        where: {ref: origin_o_r, shift: [124.470, -4.707]}
        params: {TP: VCC, R1: TX, R2: RX, SL: GND}
      - what: ceoloide/mounting_hole_plated
        where: {ref: origin_o_r, shift: [125.845, -74.520]}
        params: {drill: 2.2}
      - what: ceoloide/mounting_hole_plated
        where: {ref: origin_o_r, shift: [14.509, -84.621]}
        params: {drill: 2.2}
      - what: ceoloide/mounting_hole_plated
        where: {ref: origin_o_r, shift: [38.533, -8.069]}
        params: {drill: 2.2}
      - what: ceoloide/mounting_hole_plated
        where: {ref: origin_o_r, shift: [117.061, -8.069]}
        params: {drill: 2.2}

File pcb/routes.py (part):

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    west = {'L/DATA': 11.0, 'L/SEL0': 11.8, 'L/SEL1': 12.6, 'L/SEL2': 13.4, 'L/ADC_C': 14.2, 'L/ADC_B': 15.0}
    notch = {n: y - 7.9 for n, y in west.items()}
    east = {'L/DATA': 5.2, 'L/SEL0': 6.5, 'L/SEL1': 7.3, 'L/SEL2': 8.1, 'L/ADC_C': 8.9}
    pin = {'L/DATA': '8', 'L/SEL0': '9', 'L/SEL1': '10', 'L/SEL2': '11', 'L/ADC_C': '2', 'L/ADC_B': '3'}
    order = list(west)
    for i, n in enumerate(order):
        p = pad('MCU1', pin[n])
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            else:                                # down the corridor between the index and inner columns into IC3
                col = {'L/ADC_C': 94.3, 'L/SEL2': x('IC3', '9'), 'L/SEL1': x('IC3', '10'), 'L/SEL0': x('IC3', '11')}[n]
                pts += [(col, east[n])]
                if n == 'L/ADC_C':               # past the west end, then under the chip between its pin rows
                    z = pad('IC3', '3')
                    pts += [(col, 70.5), (z[0], 70.5), z]
                else:
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    # IC1's fan: pinky top and the ring keys from above, the rest from below, hooking round a sensor where needed
    p = lambda n: pad('IC1', n)
    e = {k: exit_(r) for k, r in (('pt', 'S1'), ('ph', 'S6'), ('pb', 'S11'), ('o', 'S16'), ('rt', 'S2'), ('rh', 'S7'), ('rb', 'S12'))}
    track('L/K_PINKY_TOP', 'B', S, [e['pt'], (e['pt'][0], 44.3), (p('2')[0] - 0.8, 44.3), p('2')], 0.6)
    track('L/K_RING_TOP', 'B', S, [e['rt'], (e['rt'][0], 26.8), (p('4')[0], 26.8 + e['rt'][0] - p('4')[0]), p('4')], 0.6)
    track('L/K_RING_HOME', 'B', S, [e['rh'], (e['rh'][0], 45.9), (44.8, 45.9), (44.8, 43.0), (p('5')[0], 43.0), p('5')], 0.6)
    track('L/K_PINKY_HOME', 'B', S, [p('14'), (p('14')[0], 54.5), (25.07, 54.5), (25.07, 63.5), (e['ph'][0], 63.5), e['ph']], 0.6)
    track('L/K_OUTER', 'B', S, [p('15'), (p('15')[0], 53.5), (20.0, 53.5), (20.0, e['o'][1]), e['o']], 0.6)
    track('L/K_PINKY_BOTTOM', 'B', S, [p('13'), (p('13')[0], 57.0), (37.9, 57.5), (37.9, 80.0), (36.3, 81.6), (e['pb'][0], 81.6), e['pb']], 0.6)
    track('L/K_RING_BOTTOM', 'B', S, [p('12'), (p('12')[0], 56.6), (45.6, 56.6), (45.6, 65.0), (e['rb'][0], 65.0), e['rb']], 0.6)

    # IC2's fan: middle keys from the west, index keys from the east
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    notch = {n: y - 7.9 for n, y in west.items()}
    after = {'R/ADC_C': 5.2, 'R/SEL2': 6.0, 'R/SEL1': 6.8, 'R/SEL0': 7.6, 'R/DATA': 8.4}
    k = {'R/ADC_C': 190.96, 'R/SEL2': 192.09, 'R/SEL1': 193.22, 'R/SEL0': 194.35, 'R/DATA': 195.48}   # descents along x + y = k
    pin = {'R/ADC_B': '3', 'R/ADC_C': '2', 'R/SEL2': '11', 'R/SEL1': '10', 'R/SEL0': '9', 'R/DATA': '8'}
    drop = {'R/SEL0': 171.0, 'R/SEL1': 170.2, 'R/SEL2': 169.4, 'R/ADC_C': 168.6}     # down the corridor into IC3
    for i, n in enumerate(west):
        p = pad('MCU101', pin[n])
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                pts += [(176.5, after[n])]
            else:
                pts += [(drop[n], after[n])]
                if n == 'R/ADC_C':               # over IC3's north end, then under the chip between its pin columns
                    z = pad('IC103', '3')
                    pts += [(drop[n], 64.3), (164.73, 64.3), (164.73, z[1]), z]
                else:
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    e = {k_: exit_(r) for k_, r in (('pt', 'S101'), ('ph', 'S106'), ('pb', 'S111'), ('o', 'S116'), ('rt', 'S102'), ('rh', 'S107'), ('rb', 'S112'))}
    track('R/K_RING_TOP', 'B', S, [e['rt'], (e['rt'][0], 26.7), (p('2')[0], 26.7 + p('2')[0] - e['rt'][0]), p('2')], 0.6)
    track('R/K_RING_HOME', 'B', S, [e['rh'], (p('1')[0] - 0.5, e['rh'][1]), p('1')], 0.6)
    track('R/K_PINKY_TOP', 'B', S, [e['pt'], (e['pt'][0], 44.0), (p('5')[0] + 0.5, 44.0), p('5')], 0.6)
    track('R/K_RING_BOTTOM', 'B', S, [p('15'), (p('15')[0], 54.4), (219.1, 58.86), (219.1, 65.0), (e['rb'][0], 65.0), e['rb']], 0.6)
    track('R/K_PINKY_HOME', 'B', S, [p('12'), (p('12')[0], 55.2), (232.5, 55.2), (233.0, 55.7), (233.0, 62.8), (e['ph'][0], 62.8), e['ph']], 0.6)
    track('R/K_OUTER', 'B', S, [p('13'), (p('13')[0], 56.0), (229.8, 56.0), (229.8, 66.0), (247.0, 66.0), (247.0, 76.6), (e['o'][0], 76.6), e['o']], 0.6)
    track('R/K_PINKY_BOTTOM', 'B', S, [p('14'), (p('14')[0], 56.8), (227.0, 56.8), (227.0, 81.6), (e['pb'][0], 81.6), e['pb']], 0.6)

    # IC2's fan
    p = lambda n: pad('IC102', n)
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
